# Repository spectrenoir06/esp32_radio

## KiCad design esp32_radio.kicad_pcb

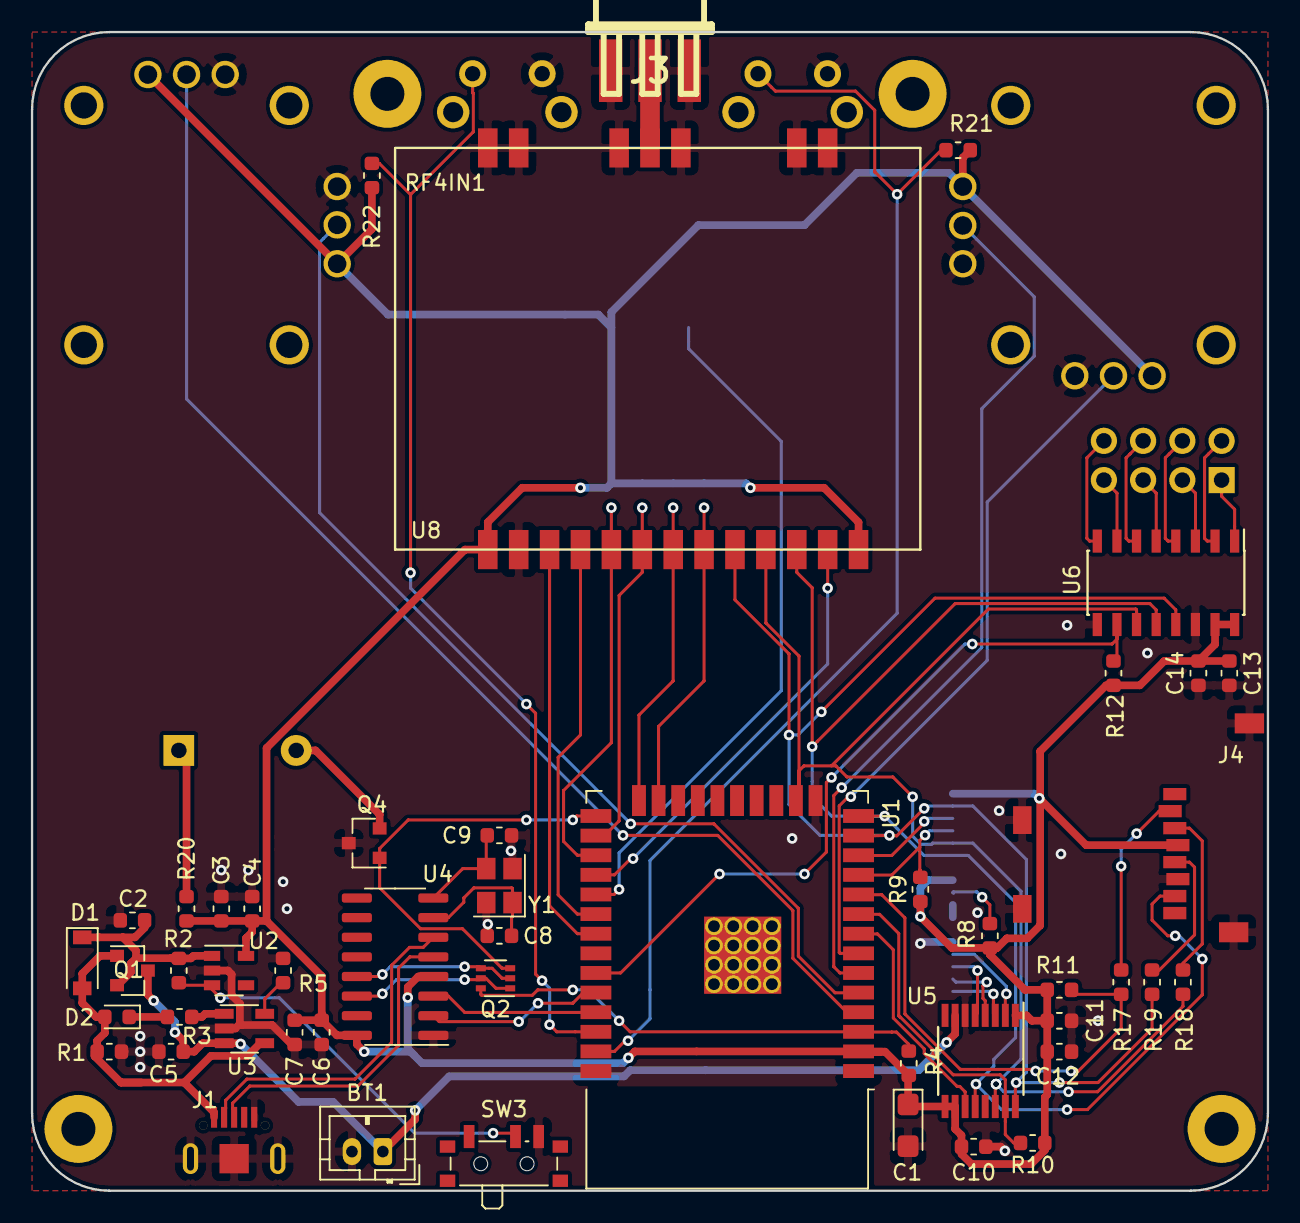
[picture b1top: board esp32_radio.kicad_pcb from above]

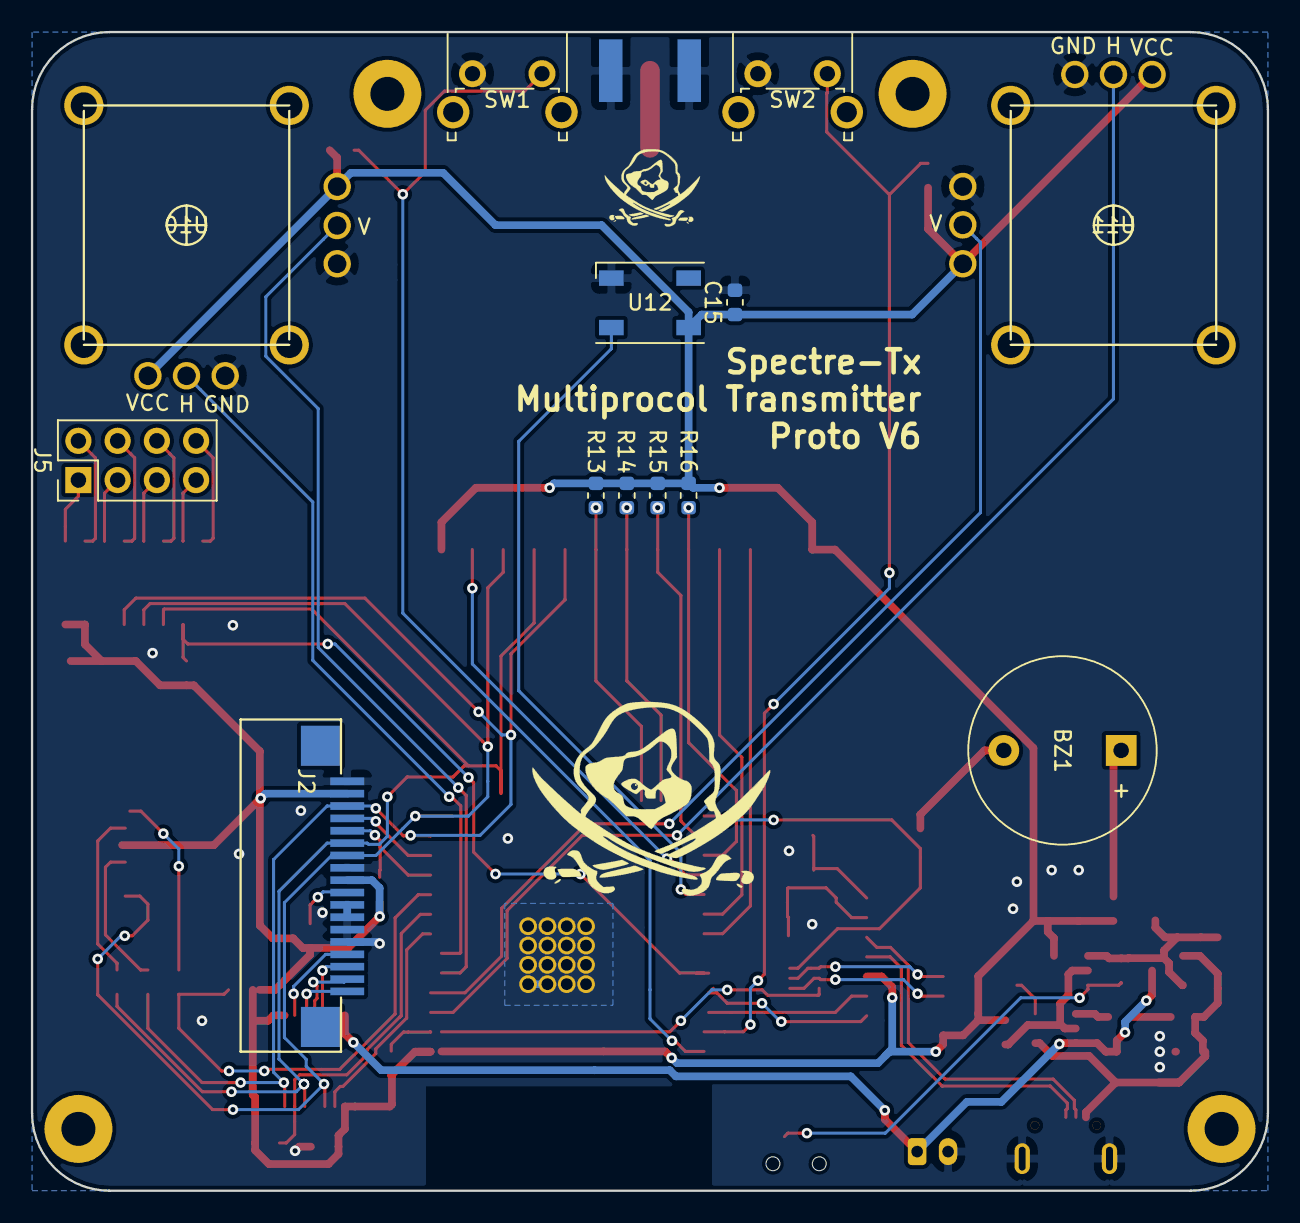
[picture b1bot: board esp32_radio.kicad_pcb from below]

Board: 2 copper layers, 80.0 x 75.0 mm, 65 parts (13 on the bottom side), 61 nets.

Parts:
BT1: 1S Battery; JST_PH_B2B-PH-K_1x02_P2.00mm_Vertical
BZ1: Buzzer; Buzzer_12x9.5RM7.6
C1: 100uF; CP_EIA-3216-12_Kemet-S
C2, C3, C5, C6, C12, C14: 10uF; C_0603_1608Metric
C4, C15: 1uF; C_0603_1608Metric
C7, C10, C11, C13: 100nF; C_0603_1608Metric
C8, C9: 22pF; C_0603_1608Metric
D1: MBR120; D_SOD-123
D2: orange; LED_0603_1608Metric
J1: USB_OTG; microUSB-smd-C40939
J2: LCD_TS; FPC_18
J3: RP-SMA; CON-SMA-EDGE
J4: Micro_SD_Card; MicroSD_C125617
J5: Conn_ADC; Pin_Header_Straight_2x04_Pitch2.54mm
MH1, MH2, MH3, MH4: MountingHole; MountingHole_2.2mm_M2_Pad
Q1: DMG3415U; SOT-23
Q2: UMH3N; SOT-363_SC-70-6
Q4: Q_NPN_BCE; SOT-23
R1, R2, R9, R10, R11, R12, R13, R14, R15, R16: 100K; R_0603_1608Metric
R3: 1k; R_0603_1608Metric
R4, R17, R18, R19, R21, R22: 10K; R_0603_1608Metric
R5: 4.7K; R_0603_1608Metric
R8: 3.9; R_0603_1608Metric
R20: 4.7; R_0603_1608Metric
SW1, SW2: SW_Push; SW_Tactile_SPST_Angled_PTS645Vx58-2LFS
SW3: SW_SPDT; SW_SPDT_PCM12
U1: ESP32-WROOM; ESP32-WROOM-32
U2: AP2112-3.3; SOT-23-5
U3: MCP73831; TSOT-23-5
U4: CH340G; SOIC-16_3.9x9.9mm_P1.27mm
U5: XPT2046TS; TSSOP-16_4.4x5mm_Pitch0.65mm
U6: MCP3008; SOIC-16_3.9x9.9mm_Pitch1.27mm
U8: RF4IN1
U10, U11: Joystick; Joystick_raider
U12: WS2812B; LED_WS2812B-PLCC4
Y1: 12MHz; Crystal_SMD_3225-4Pin_3.2x2.5mm

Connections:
+3V3: C1.1, C3.1, C4.1, C6.1, C7.1, C10.1, C11.1, C12.1, C13.1, C14.1, C15.1, J2.2, J2.9, J4.4, R4.1, R8.1, R9.1, R10.1, R11.1, R12.1, R13.1, R14.1, R15.1, R16.1, R20.2, R21.1, R22.1, U1.2, U2.5, U4.4, U4.16, U5.1, U5.9, U5.10, U6.15, U6.16, U8.1, U8.20, U10.1, U10.4, U11.1, U11.4, U12.1
/B_L: R21.2, SW1.2, U1.37
/B_R: R22.2, SW2.2, U1.36
/CS_A7105: R16.2, U1.27, U8.5
/CS_ADC: R12.2, U1.33, U6.10
/CS_CC25: R15.2, U1.26, U8.6
/CS_CYRF: R13.2, U1.23, U8.8
/CS_LCD: J2.5, R9.2, U1.11
/CS_NRF24: R14.2, U1.24, U8.7
/CS_SD: R11.2, R17.1, U1.10
/CS_TOUCH: R10.2, U1.9, U5.15
/CYRF_RST: U1.28, U8.12
/D+: J1.3, U4.5
/D-: J1.2, U4.6
/DTR: Q2.2, Q2.4, U4.13
/EXT_ADC_CH0: J5.1, U6.1
/EXT_ADC_CH1: J5.2, U6.2
/EXT_ADC_CH2: J5.3, U6.3
/EXT_ADC_CH3: J5.4, U6.4
/EXT_ADC_CH4: J5.5, U6.5
/EXT_ADC_CH5: J5.6, U6.6
/EXT_ADC_CH6: J5.7, U6.7
/EXT_ADC_CH7: J5.8, U6.8
/GPIO_0: Q2.3, Q4.1, U1.25
/INT_ADC_CH0: U1.4, U11.2
/INT_ADC_CH1: U1.5, U11.5
/INT_ADC_CH2: U1.6, U10.5
/INT_ADC_CH3: U1.7, U10.2
/LCD_CMD: J2.4, U1.12
/MISO: J2.7, J4.7, U1.14, U5.12, U6.12, U8.11
/MOSI: J2.6, R18.2, U1.16, U5.14, U6.11, U8.10
/NEOPIXEL: U1.29, U12.4
/PE1: U1.31, U8.3
/PE2: U1.30, U8.4
/POWER: R2.2, SW3.2, U2.3
/RESET: Q2.6, R4.2, U1.3
/RTS: Q2.1, Q2.5, U4.14
/RX0: U1.34, U4.2
/SCK: J2.3, R19.2, U1.13, U5.16, U6.13, U8.9
/TS_IRQ: U1.8, U5.11
/TS_X+: J2.15, U5.2
/TS_X-: J2.17, U5.4
/TS_Y+: J2.18, U5.3
/TS_Y-: J2.16, U5.5
/TX0: U1.35, U4.3
GND: BT1.2, C1.2, C2.2, C3.2, C4.2, C5.2, C6.2, C7.2, C8.2, C9.2, C10.2, C11.2, C12.2, C13.2, C14.2, C15.2, J1.5, J1.6, J2.1, J2.8, J2.11, J2.12, J2.13, J2.14, J3.2, J3.3, J3.4, J3.5, J4.6, J4.9, Q4.3, R1.2, R5.1, SW1.1, SW2.1, SW3.3, U1.1, U1.15, U1.38, U1.39, U2.2, U3.2, U4.1, U5.6, U6.9, U6.14, U8.2, U8.13, U8.14, U8.15, U8.17, U8.18, U8.19, U10.3, U10.6, U11.3, U11.6, U12.3, Y1.2, Y1.4
unnamed: BZ1.1, R20.1
unnamed: BZ1.2, Q4.2
unnamed: C2.1, D1.1, Q1.2, R2.1, U2.1
unnamed: C8.1, U4.7, Y1.1
unnamed: C9.1, U4.8, Y1.3
unnamed: D2.1, R3.2
unnamed: J2.10, R8.2
unnamed: J3.1, U8.16
unnamed: J4.2, R17.2
unnamed: J4.3, R18.1
unnamed: J4.5, R19.1
unnamed: R3.1, U3.1
unnamed: R5.2, U3.5
VBAT: BT1.1, C5.1, Q1.3, U3.3, U5.7
VBUS: D1.2, D2.2, J1.1, Q1.1, R1.1, U3.4

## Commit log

2017-11-16 init
2018-02-07 change laptop
2018-04-08 fix nrf24l01 output + remove i2c + working i2s
2018-04-08 clean shematic
2018-04-08 lolin32+LCDShield
2018-04-08 osh v3
2018-04-08 image
2018-04-22 fix mosi near edge + fix nrf24 shematic + fix RF4in1 footprint
2018-04-22 update esp32
2018-04-24 clean
2018-04-24 update bom
2018-04-25 v4 root
2018-04-25 rf tunning
2018-04-25 logo
2018-04-26 doom proof
2018-04-26 test
2018-04-27 add cc2500 + reset button + capa on TS
2018-06-02 drill circular
2018-06-03 pull up + gerber
2018-09-28 test 3d + 5.0
2018-12-25 update 0603
2018-12-25 root
2019-01-31 add 3d + fix mosfet
2020-05-16 update doc
2020-05-16 maj doc
2020-05-16 remove net
2020-05-16 big clean
